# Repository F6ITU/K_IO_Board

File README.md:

# K_IO_Board
LA2NI's OpenHPSDR I/O Board (Kicad Version)

OpenHPSDR P.A. OpenHPSDR Input/Output board by LA2NI (Munin 400)

This picture shows an early design of the I/O board by LA2NI

This I/O board is part of a set consisting of a 400 W LDMos based RF power amplifier (Munin 400), 
a medium power (600 or 1500 W) Zolotarev low pass filter, an Automatic Antenna Tuner (ATU) nickname « Aries » 
and a 4 port antenna switch.

All these developments are the work and intellectual property of Kjell Karlsen LA2NI and Laurence Barker G8NJJ.

This original work can be downloaded from 

https://github.com/LA2NI/

https://github.com/laurencebarker

The I/O board ensures the physical link between the transceiver and the "Munin400/Aries" RF system

For more information, please refer to the Aries documentation (in the G8NJJ github repository)

This board was originally developed in September 2021 by Kjell LA2NI , with UltiBoard EDA. A very early release has been designed
using KiCAD EDA. After some test on a prototype setup, it has been decided to extend this board to offer both P1/output jack and
the full set of J1 signal output and a 12V switched power supply rail for the OpenHPSDR Andromeda interface. All internal or external
"tune" trace that can be found on the original f5 release of the I/O board schematic have been deleted

This design is protected by the CERN Open source/ Open hardware Licence.

Kicad is an Opensource EDA software maintained by the European Reseach Center CERN (Conseil européen pour la recherche nucléaire)

The original work is protected by the TAPR Open Hardware licence

Gerber files could be downloaded at https://github.com/F6ITU/K_IO_Board/tree/main/Gerber 

An interactive BOM is also available https://github.com/F6ITU/K_IO_Board/tree/main/iBom

This version is -so far- considered as a "final and usable" version. As usual, all improvement suggestions are welcome.

73' , Enjoy

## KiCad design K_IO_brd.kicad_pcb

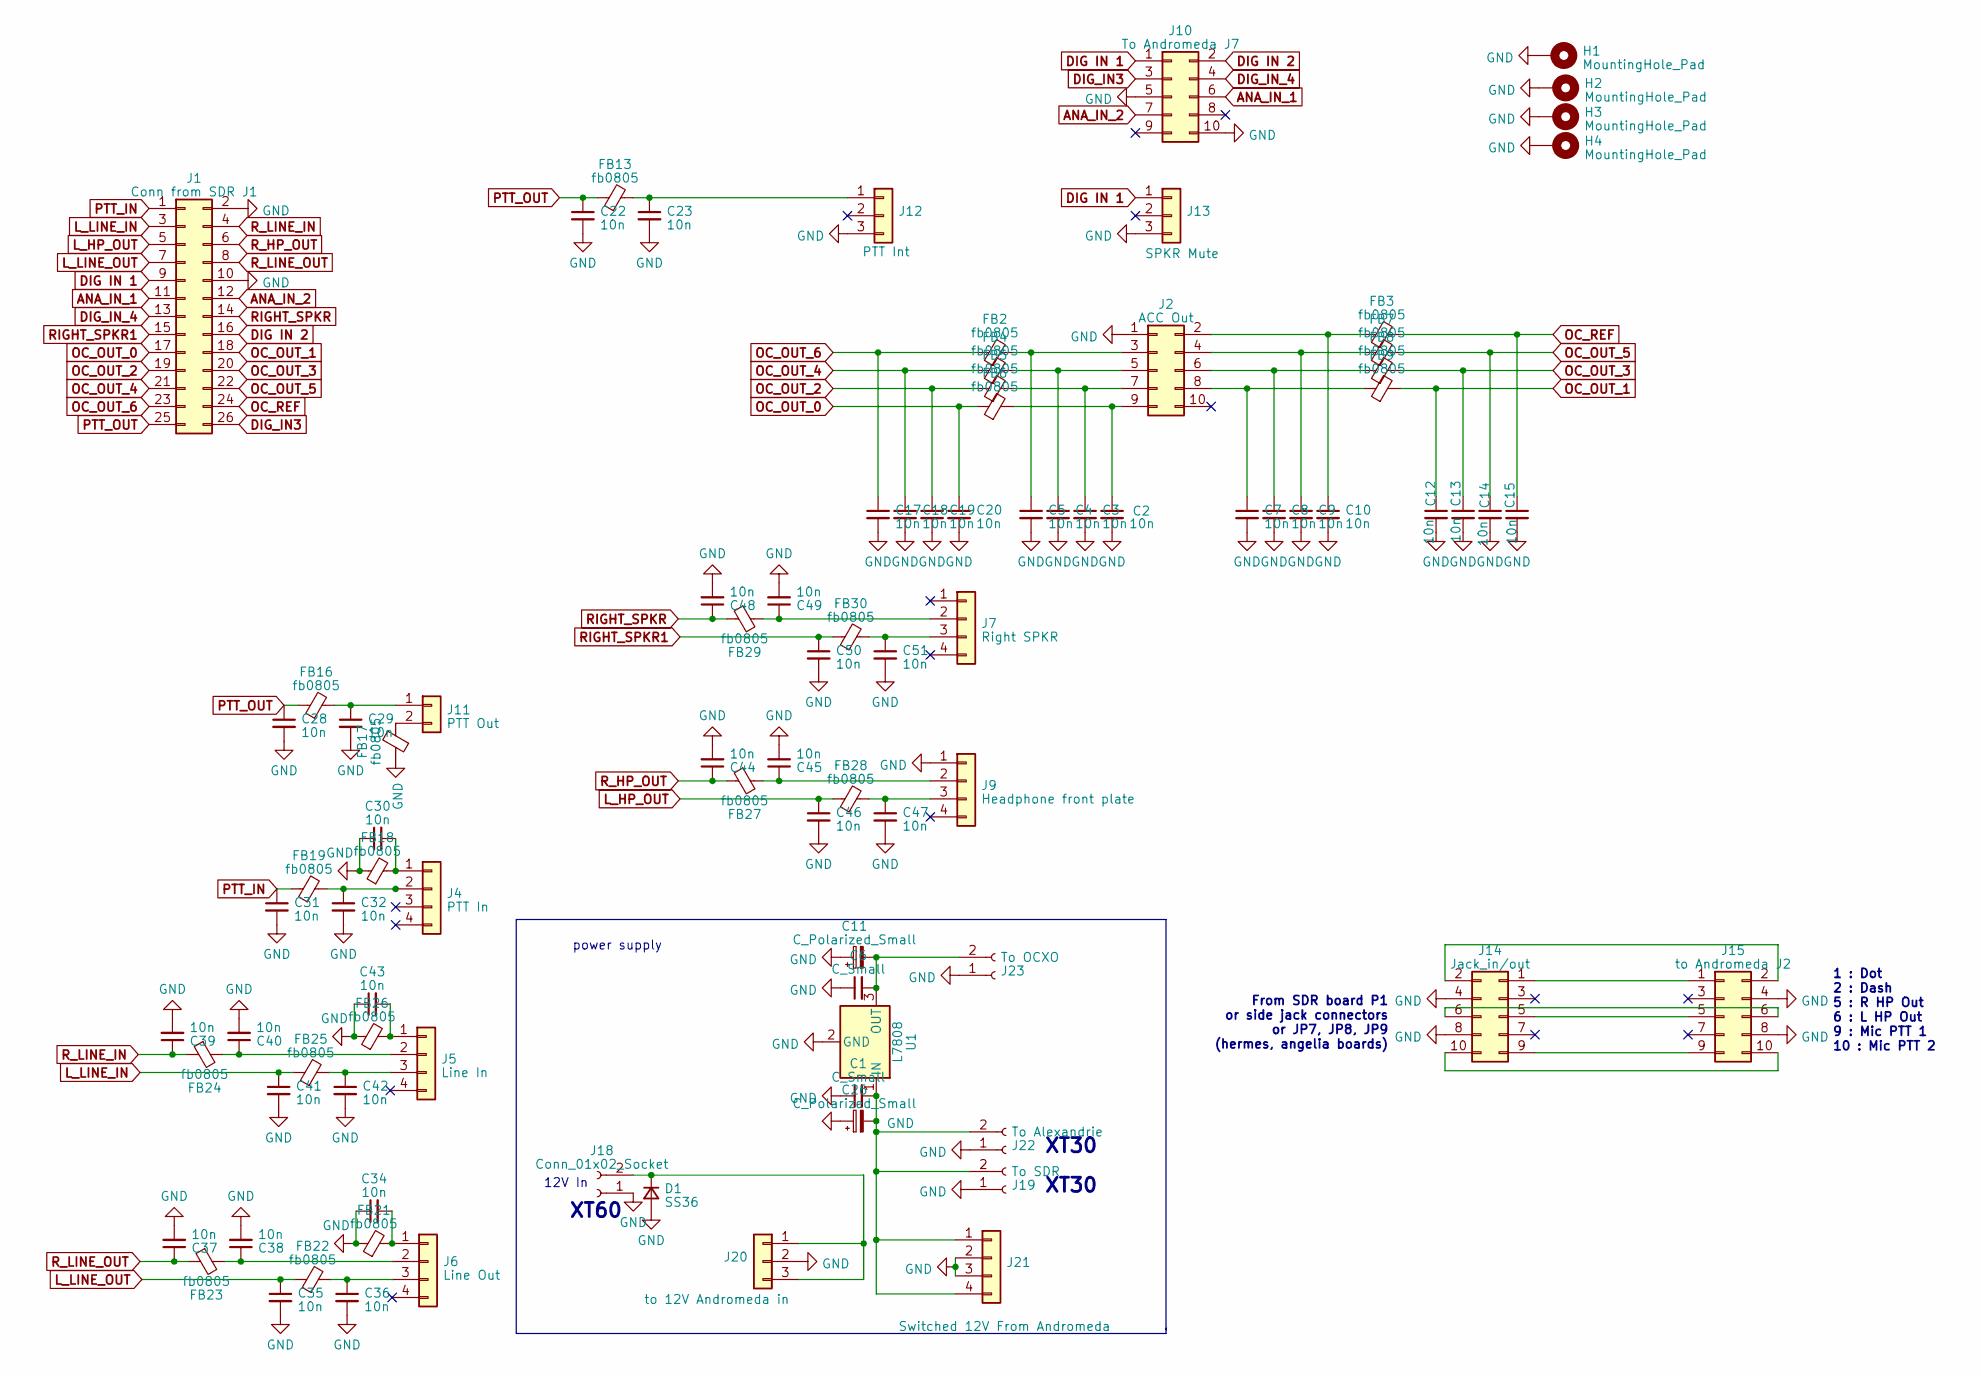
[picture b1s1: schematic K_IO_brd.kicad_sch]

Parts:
C1, C6: C_Small; C_0805_2012Metric_Pad1.18x1.45mm_HandSolder
C2, C3, C4, C5, C7, C8, C9, C10, C12, C13, C14, C15, C17, C18, C19, C20, C22, C23, C28, C29, C30, C31, C32, C34, C35, C36, C37, C38, C39, C40, C41, C42, C43, C44, C45, C46, C47, C48, C49, C50, C51: 10n; C_0805_2012Metric_Pad1.18x1.45mm_HandSolder
C11, C26: C_Polarized_Small; C_2220_5650Metric_Pad1.97x5.40mm_HandSolder
D1: SS36; D_SMC
FB2, FB3, FB4, FB5, FB6, FB7, FB8, FB9, FB13, FB16, FB17, FB18, FB19, FB21, FB22, FB23, FB24, FB25, FB26, FB27, FB28, FB29, FB30: fb0805; L_0805_2012Metric_Pad1.15x1.40mm_HandSolder
H1, H2, H3, H4: MountingHole_Pad; MountingHole_3.5mm_Pad_Via
J1: Conn from SDR J1; IDC-Header_2x13_P2.54mm_Vertical
J2: ACC Out; IDC-Header_2x05_P2.54mm_Vertical
J4: PTT In; Molex_KK-254_AE-6410-04A_1x04_P2.54mm_Vertical
J5: Line In; Molex_KK-254_AE-6410-04A_1x04_P2.54mm_Vertical
J6: Line Out; Molex_KK-254_AE-6410-04A_1x04_P2.54mm_Vertical
J7: Right SPKR; Molex_KK-254_AE-6410-04A_1x04_P2.54mm_Vertical
J9: Headphone front plate; Molex_KK-254_AE-6410-04A_1x04_P2.54mm_Vertical
J10: To Andromeda J7; IDC-Header_2x05_P2.54mm_Vertical
J11: PTT Out; Molex_KK-254_AE-6410-02A_1x02_P2.54mm_Vertical
J12: PTT Int; Molex_KK-254_AE-6410-03A_1x03_P2.54mm_Vertical
J13: SPKR Mute; Molex_KK-254_AE-6410-03A_1x03_P2.54mm_Vertical
J14: Jack_in/out; IDC-Header_2x05_P2.54mm_Vertical
J15: to Andromeda J2; IDC-Header_2x05_P2.54mm_Vertical
J18: Conn_01x02_Socket; AMASS_XT30U-F_1x02_P5.0mm_Vertical
J19: To SDR; AMASS_XT30U-F_1x02_P5.0mm_Vertical
J20: to 12V Andromeda in; Molex_KK-254_AE-6410-03A_1x03_P2.54mm_Vertical
J21: Switched 12V From Andromeda; Molex_KK-254_AE-6410-04A_1x04_P2.54mm_Vertical
J22: To Alexandrie; AMASS_XT30U-F_1x02_P5.0mm_Vertical
J23: To OCXO; Molex_KK-254_AE-6410-02A_1x02_P2.54mm_Vertical
U1: L7808; TO-252-3_TabPin2

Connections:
ANA_IN_1: J1.11, J10.6
ANA_IN_2: J1.12, J10.7
DIG IN 1: J1.9, J10.1, J13.1
DIG IN 2: J1.16, J10.2
DIG_IN3: J1.26, J10.3
DIG_IN_4: J1.13, J10.4
GND: C1.1, C2.2, C3.2, C4.2, C5.2, C6.1, C7.2, C8.2, C9.2, C10.2, C11.1, C12.2, C13.2, C14.2, C15.2, C17.2, C18.2, C19.2, C20.2, C22.2, C23.2, C26.1, C28.2, C29.2, C30.1, C31.2, C32.2, C34.1, C35.2, C36.2, C37.2, C38.2, C39.2, C40.2, C41.2, C42.2, C43.1, C44.2, C45.2, C46.2, C47.2, C48.2, C49.2, C50.2, C51.2, D1.2 (A), FB17.1, FB18.1, FB21.1, FB26.1, H1.1, H2.1, H3.1, H4.1, J1.2, J1.10, J2.1, J9.1, J10.5, J10.10, J12.3, J13.3, J14.4, J14.8, J15.4, J15.8, J18.1, J19.1, J20.2, J21.2, J21.3, J22.1, J23.1, U1.2 (GND)
L_HP_OUT: C46.1, FB28.1, J1.5
L_LINE_IN: C41.1, FB25.1, J1.3
L_LINE_OUT: C35.1, FB22.1, J1.7
unnamed: D1.1 (K), J18.2, J20.1, J20.3
unnamed: C10.1, FB3.1, J2.2
unnamed: C5.1, FB2.2, J2.3
unnamed: C9.1, FB7.1, J2.4
unnamed: C4.1, FB4.2, J2.5
unnamed: C8.1, FB8.1, J2.6
unnamed: C3.1, FB5.2, J2.7
unnamed: C7.1, FB9.1, J2.8
unnamed: C2.1, FB6.2, J2.9
unnamed: C30.2, FB18.2, J4.1
unnamed: C32.1, FB19.2, J4.2
unnamed: C43.2, FB26.2, J5.1
unnamed: C40.1, FB24.2, J5.2
unnamed: C42.1, FB25.2, J5.3
unnamed: C34.2, FB21.2, J6.1
unnamed: C38.1, FB23.2, J6.2
unnamed: C36.1, FB22.2, J6.3
unnamed: C49.1, FB29.2, J7.2
unnamed: C51.1, FB30.2, J7.3
unnamed: C45.1, FB27.2, J9.2
unnamed: C47.1, FB28.2, J9.3
unnamed: C29.1, FB16.2, J11.1
unnamed: FB17.2, J11.2
unnamed: C23.1, FB13.2, J12.1
unnamed: J14.1, J15.1
unnamed: J14.2, J15.2
unnamed: J14.5, J15.5
unnamed: J14.6, J15.6
unnamed: J14.9, J15.9
unnamed: J14.10, J15.10
unnamed: C1.2, C26.2, J19.2, J21.1, J21.4, J22.2, U1.1 (IN)
unnamed: C6.2, C11.2, J23.2, U1.3 (OUT)
OC_OUT_0: C20.1, FB6.1, J1.17
OC_OUT_1: C12.1, FB9.2, J1.18
OC_OUT_2: C19.1, FB5.1, J1.19
OC_OUT_3: C13.1, FB8.2, J1.20
OC_OUT_4: C18.1, FB4.1, J1.21
OC_OUT_5: C14.1, FB7.2, J1.22
OC_OUT_6: C17.1, FB2.1, J1.23
OC_REF: C15.1, FB3.2, J1.24
PTT_IN: C31.1, FB19.1, J1.1
PTT_OUT: C22.1, C28.1, FB13.1, FB16.1, J1.25
RIGHT_SPKR: C48.1, FB29.1, J1.14
RIGHT_SPKR1: C50.1, FB30.1, J1.15
R_HP_OUT: C44.1, FB27.1, J1.6
R_LINE_IN: C39.1, FB24.1, J1.4
R_LINE_OUT: C37.1, FB23.1, J1.8

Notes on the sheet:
XT60
power supply
XT30
12V In
1 : Dot 2 : Dash 5 : R HP Out 6 : L HP Out 9 : Mic PTT 1 10 : Mic PTT 2
From SDR board P1 or side jack connectors or JP7, JP8, JP9 (hermes, angelia boards)

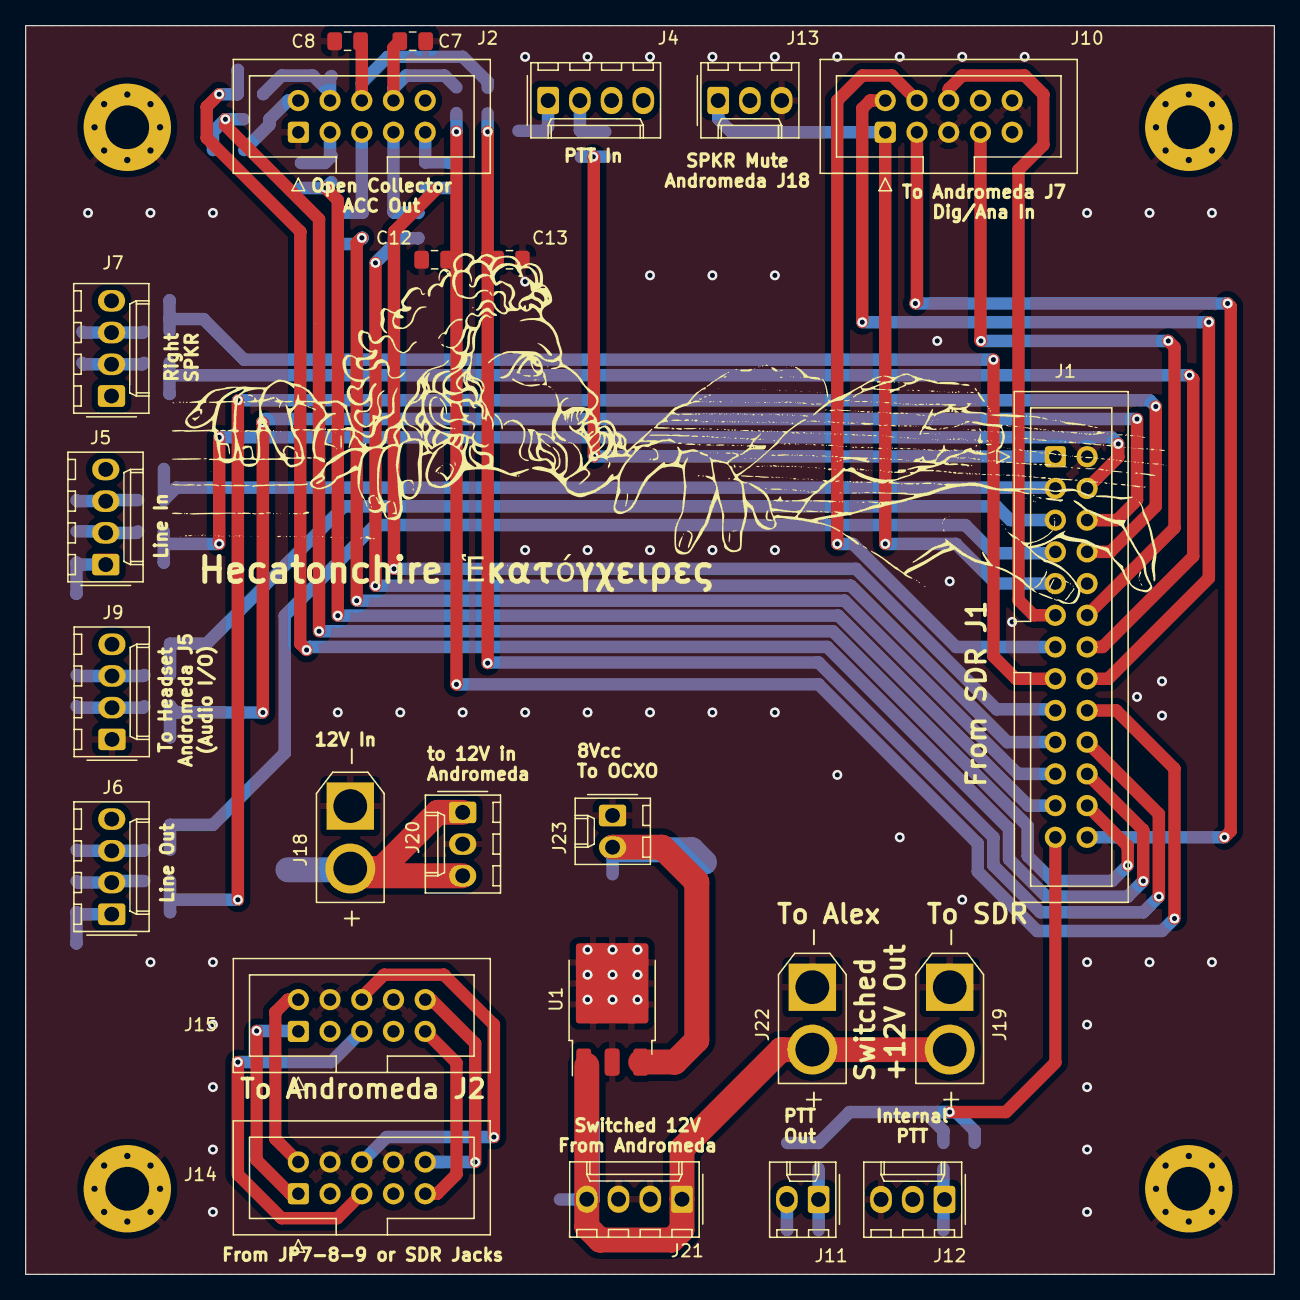
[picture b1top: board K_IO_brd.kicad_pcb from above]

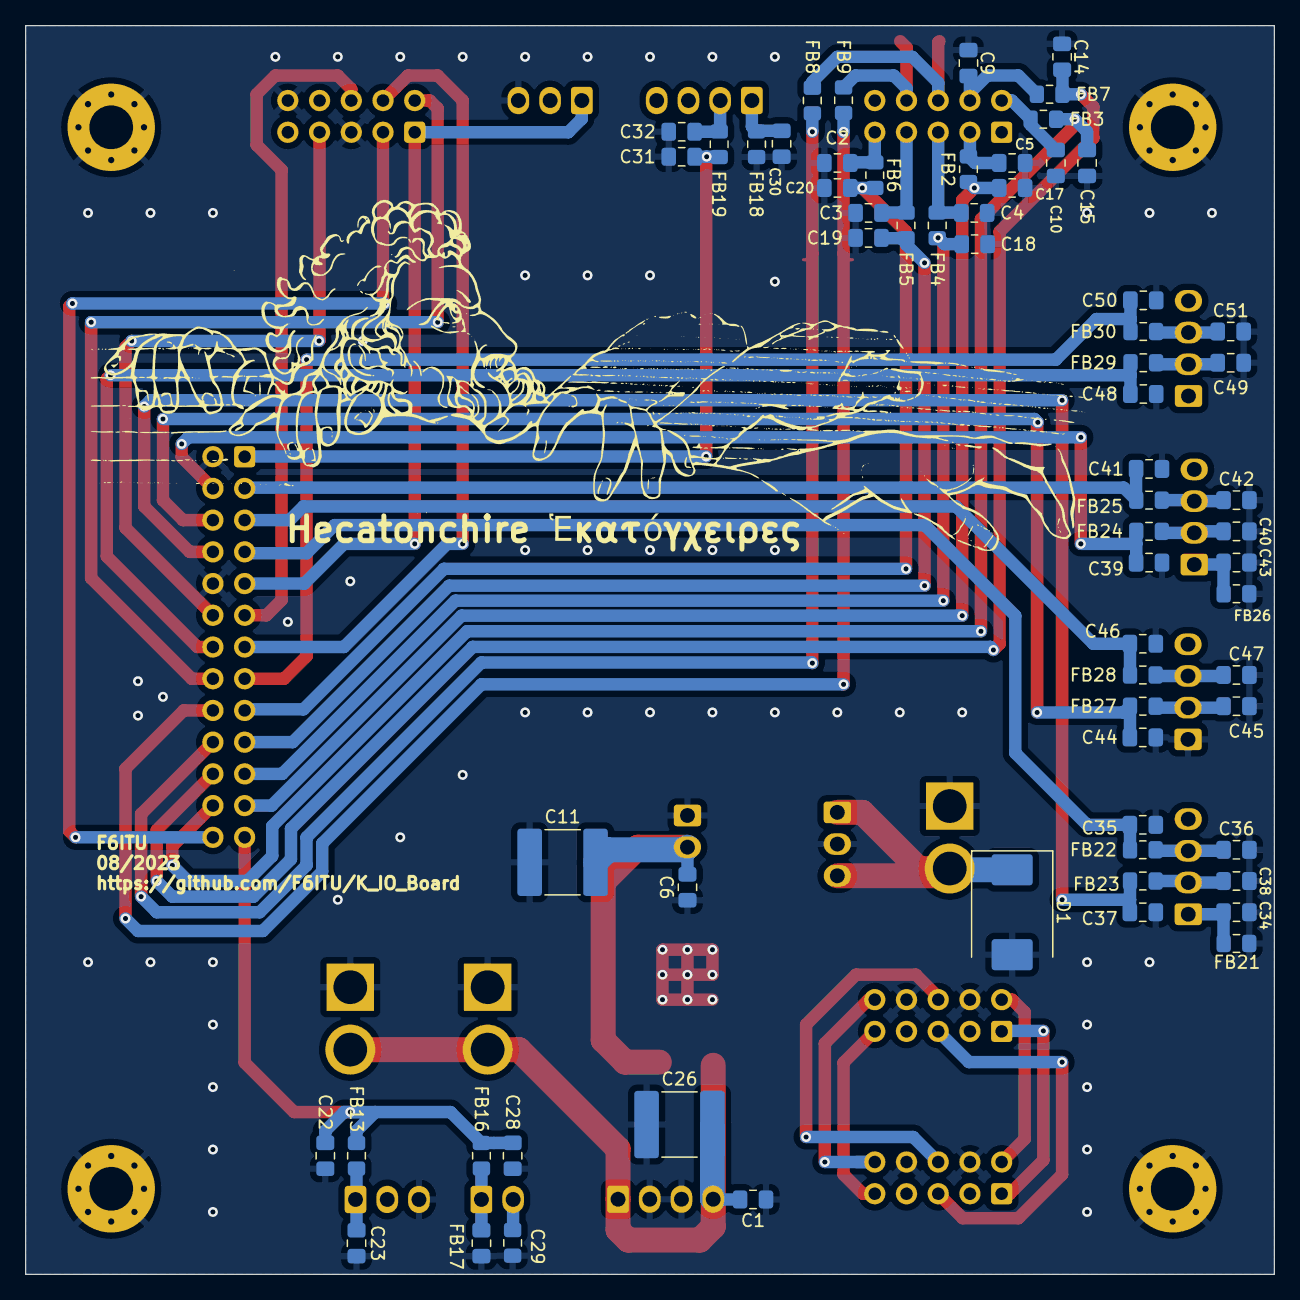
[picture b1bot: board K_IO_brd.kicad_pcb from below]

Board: 2 copper layers, 100.0 x 100.0 mm, 93 parts (65 on the bottom side), 57 nets.

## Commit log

2023-05-13 first commit, new README
2023-08-12 major change, full J1 support, 10c10 board
2023-08-23 minor changes
2023-08-23 new readme, working release
